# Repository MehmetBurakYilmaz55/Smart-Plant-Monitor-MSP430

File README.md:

# Akıllı Tarım Otomasyonu ve Gömülü Kontrol Sistemi (MSP430)

Bu proje, bir bitkinin çevresel ihtiyaçlarını (nem, sıcaklık, ışık) sürekli olarak analiz edip gerekli fiziksel müdahaleleri (sulama, yapay aydınlatma) otonom olarak gerçekleştiren donanım merkezli bir gömülü sistem projesidir. 

Projenin temel amacı, piyasadaki hazır sensör ve güç modülleri (breakout board) kullanım alışkanlıklarını bir kenara bırakarak; voltaj regülasyonundan güç anahtarlamaya kadar tüm elektriksel altyapının özel tasarlanmış **çift taraflı bir PCB** üzerinde komponent seviyesinde (component-level) birleştirilmesidir. Yazılım mimarisinde ise hiçbir soyutlama kütüphanesi (HAL veya standart kütüphane) kullanılmamış, doğrudan mikrodenetleyici register'larına müdahale edilmiştir.

---

## 🛠️ Donanım Mimarisi ve Çift Taraflı PCB Tasarımı

Sistemin en güçlü yönü, elektriksel bütünlüğü ve kararlılığı maksimize etmek amacıyla baştan sona özel olarak tasarlanan donanım altyapısıdır. Piyasada sıkça tercih edilen hazır modüllerden (Bluetooth ve OLED ekran hariç) tamamen kaçınılmış, sistem donanım seviyesinde sıfırdan kurgulanmıştır.

* **Çift Taraflı (Double-Sided) Özelleştirilmiş PCB:** Sinyal yolları ve yüksek akım çeken güç hatları, elektromanyetik girişimi (EMI) minimize edecek şekilde iki katmanlı olarak yönlendirilmiştir.
* **Tümleşik Voltaj Regülasyonu:** Harici bir güç modülü kullanılmaksızın, giriş gerilimini mikrodenetleyicinin ve sensörlerin ihtiyaç duyduğu kararlı 3.3V seviyesine düşüren lineer regülatör devresi doğrudan PCB üzerine gömülmüştür.
* **Komponent Seviyesinde Tasarım:** Hazır röle veya sensör kartları kullanılmamıştır. Su pompasını süren rölenin transistör tabanlı sürücü devresi (demeraj ve ters EMK korumaları dahil) ile sensör okuma hatlarının sinyal koşullandırma devreleri PCB üzerinde bağımsız komponentlerle dizayn edilmiştir.
* **Fiziksel Dayanım:** Ortam şartlarına ve elektromekanik titreşimlere karşı dirençli bir endüstriyel prototip elde edilmiştir.

---

## 💻 Yazılım Mimarisi (Bare-Metal)

Sistemin yazılımı, MSP430G2553 mikrodenetleyicisinin tüm kaynaklarını %100 kontrol edebilmek amacıyla tamamen **"Bare-Metal"** (kütüphanesiz) olarak C dilinde geliştirilmiştir.

* **Register-Level Programlama:** I2C, UART, ADC ve Timer donanımları hazır kütüphanelerle değil, doğrudan işlemci kaydedicileri (register) üzerinden bayt bayt yapılandırılmıştır.
* **Özel I2C ve OLED Sürücüsü:** SSD1306 OLED ekranı kontrol etmek için donanımsal I2C protokolü ve 5x8 ASCII font matrisi sıfırdan yazılarak sisteme entegre edilmiştir.
* **Donanımsal PWM Üretimi:** İşlemciyi döngüsel gecikmelerle (delay) yormamak adına, Timer_A modülü "Reset/Set" modunda (OUTMOD_7) çalıştırılarak pürüzsüz ve işlemciden bağımsız bir PWM sinyali elde edilmiştir.
* **Dinamik Sağlık Algoritması:** Sensörlerden alınan ham ADC verileri, lineer azalan ölçeklendirme matematiksel modeli ile işlenerek bitkinin anlık durumunu gösteren dinamik bir "Büyüme Kalitesi Puanına" dönüştürülür.
* **Histerezis Kontrolü:** Röle tetiklemelerinde sistemin kararsızlığa düşmesini (chatter effect) engellemek için yazılımsal ölü bölgeler (dead-zones) oluşturulmuştur.

---

## ⚙️ Temel Özellikler ve Otonom Fonksiyonlar

* **Akıllı Sulama:** Toprak nemi belirlenen kritik eşiğin altına düştüğünde su pompası devreye girer, ideal neme ulaşıldığında histerezis bandı sayesinde güvenli bir şekilde kapanır.
* **Ters Orantılı Aydınlatma:** Ortamdaki ışık (LDR) seviyesi düştükçe, PWM kontrollü yapay aydınlatma modülü otomatik olarak parlaklığını artırır.
* **Gerçek Zamanlı Telemetri:** Tüm sensör verileri, hesaplanan kalite puanı ve röle durumları Bluetooth (UART) üzerinden kablosuz olarak aktarılır.
* **Lokal Arayüz:** İşlenen veriler ve puan durumu, cihaz üzerindeki OLED ekranda anlık olarak görüntülenir.

---

## 🚀 Kullanılan Teknolojiler ve Bileşenler

* **Mikrodenetleyici:** Texas Instruments MSP430G2553
* **Sensör Ağı:** NTC (Sıcaklık), Analog Toprak Nemi Sensörü, LDR (Ortam Işığı)
* **Aktüatörler:** 5V Su Pompası (Transistör sürücülü röle ile kontrol edilir), LED Aydınlatma (Timer_A PWM destekli)
* **Haberleşme:** HC-05 / UART Bluetooth Modülü (Sadece modül olarak kullanılmıştır)
* **Görüntüleme:** 0.96" SSD1306 OLED (I2C) (Sadece modül olarak kullanılmıştır)
* **Geliştirme Ortamı:** Code Composer Studio (CCS)
* **PCB Tasarım:** KiCad

---

## 📂 Dosya ve Klasör Yapısı

Projenin donanım tasarımı, üretim çıktıları ve yazılım kaynak kodları modüler bir yapıda organize edilmiştir:

* **`C/`**: Sistemin beyni olan yazılımın bulunduğu dizindir. Herhangi bir hazır kütüphane kullanılmadan doğrudan register seviyesinde yazılmış Bare-Metal C kaynak kodlarını içerir.
* **`Docs/`**: Donanım tasarımının mutfağıdır. Devrenin **KiCad** üzerinde sıfırdan çizilmiş elektronik şematiklerini, çift taraflı PCB yerleşim (layout) planlarını ve lazer kazıma yöntemiyle üretime hazır hale getirilmiş ön/arka bakır (Cu) yüzey PDF çıktılarını barındırır.
* **`Images/`**: Teorik tasarımın fiziksel bir ürüne dönüşme serüvenini belgeler. Lazer kazıma makinesindeki üretim aşamalarından, montajı ve lehimlemesi bitmiş çift taraflı kartın detaylı fotoğraflarına kadar projenin donanımsal kalitesini gösteren görsel dökümanları içerir.

---

## 👨‍💻 Geliştirici

**Mehmet Burak Yılmaz** 
Kocaeli Üniversitesi - Elektronik ve Haberleşme Mühendisliği

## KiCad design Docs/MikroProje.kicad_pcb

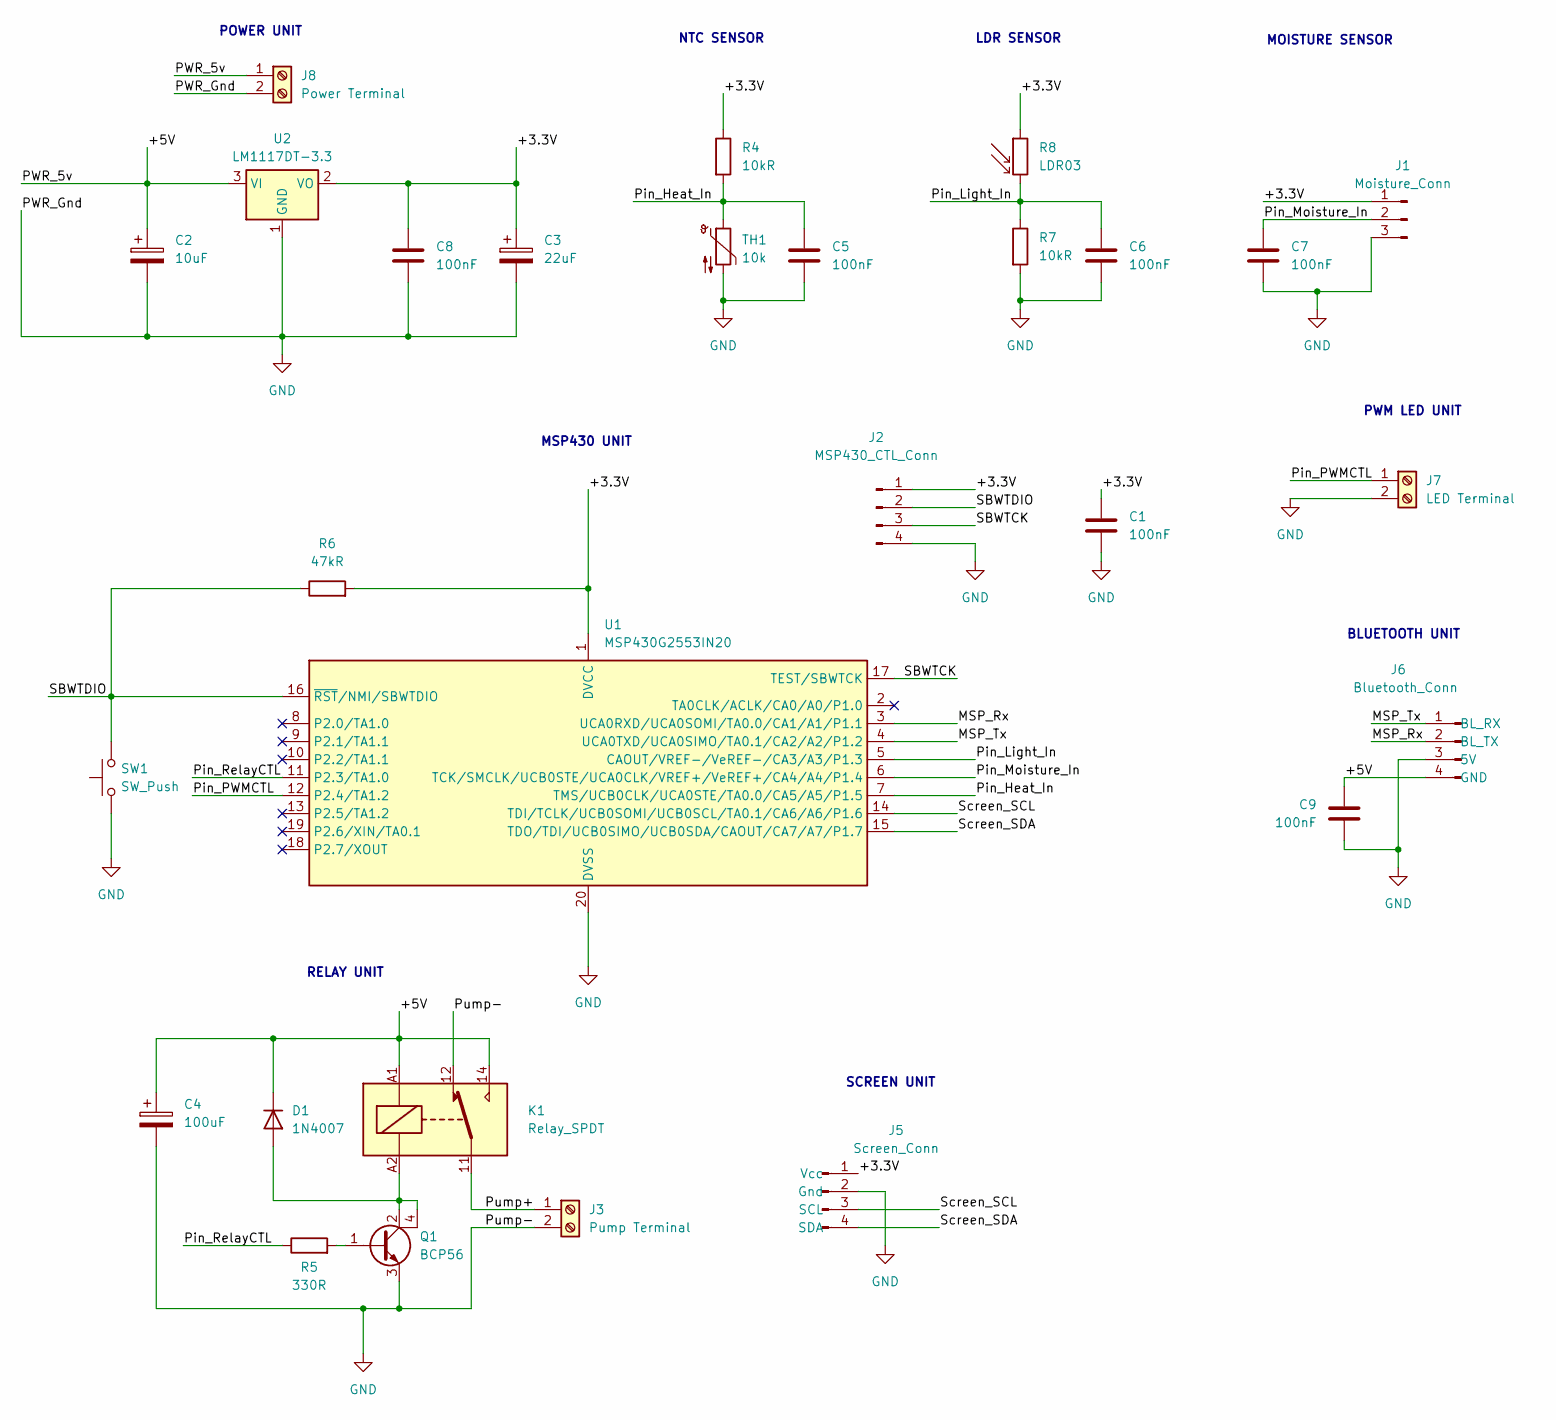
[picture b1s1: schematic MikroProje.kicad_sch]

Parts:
C1, C5, C6, C7, C8, C9: 100nF; C_1206_3216Metric_Pad1.33x1.80mm_HandSolder
C2: 10uF; CP_EIA-3528-21_Kemet-B_HandSolder
C3: 22uF; CP_EIA-3528-21_Kemet-B_HandSolder
C4: 100uF; CP_Radial_D5.0mm_P2.00mm
D1: 1N4007; D_SMA_Handsoldering
J1: Moisture_Conn; PinSocket_1x03_P2.54mm_Vertical
J2: MSP430_CTL_Conn; PinHeader_1x04_P2.54mm_Vertical
J3: Pump Terminal; TerminalBlock_Phoenix_MKDS-1,5-2-5.08_1x02_P5.08mm_Horizont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
J5: Screen_Conn; PinSocket_1x04_P2.54mm_Vertical
J6: Bluetooth_Conn; PinSocket_1x04_P2.54mm_Vertical
J7: LED Terminal; TerminalBlock_Phoenix_MKDS-1,5-2-5.08_1x02_P5.08mm_Horizont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
J8: Power Terminal; TerminalBlock_Phoenix_MKDS-1,5-2-5.08_1x02_P5.08mm_Horizont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
K1: Relay_SPDT; Relay_SPDT_Finder_32.21-x000
Q1: BCP56; SOT-223
R4, R7: 10kR; R_1206_3216Metric_Pad1.30x1.75mm_HandSolder
R5: 330R; R_1206_3216Metric_Pad1.30x1.75mm_HandSolder
R6: 47kR; R_1206_3216Metric_Pad1.30x1.75mm_HandSolder
R8: LDR03; R_LDR_5.0x4.1mm_P3mm_Vertical
SW1: SW_Push; SW_SPST_B3S-1000
TH1: 10k; R_1206_3216Metric_Pad1.30x1.75mm_HandSolder
U1: MSP430G2553IN20; DIP-20_W7.62mm
U2: LM1117DT-3.3; SOT-223-3_TabPin2

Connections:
/+3.3V: C1.1, C3.1, C8.1, J1.1, J2.1, J5.1 (Vcc), R4.1, R6.2, R8.1, U1.1 (DVCC), U2.2 (VO)
/+5V: C2.1, C4.1, C9.1, D1.1 (K), J6.4 (GND), J8.1, K1.14, K1.A1, U2.3 (VI)
/MSP_Rx: J6.2 (BL_TX), U1.3 (UCA0RXD/UCA0SOMI/TA0.0/CA1/A1/P1.1)
/MSP_Tx: J6.1 (BL_RX), U1.4 (UCA0TXD/UCA0SIMO/TA0.1/CA2/A2/P1.2)
/Pin_Heat_In: C5.1, R4.2, TH1.1, U1.7 (TMS/UCB0CLK/UCA0STE/TA0.0/CA5/A5/P1.5)
/Pin_Light_In: C6.1, R7.1, R8.2, U1.5 (CAOUT/VREF-/VeREF-/CA3/A3/P1.3)
/Pin_Moisture_In: C7.1, J1.2, U1.6 (TCK/SMCLK/UCB0STE/UCA0CLK/VREF+/VeREF+/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)
/Pin_PWMCTL: J7.1, U1.12 (P2.4/TA1.2)
/Pin_RelayCTL: R5.1, U1.11 (P2.3/TA1.0)
/Pump+: J3.1, K1.11
/SBWTCK: J2.3, U1.17 (TEST/SBWTCK)
/SBWTDIO: J2.2, R6.1, SW1.2, U1.16 (~RST/NMI/SBWTDIO)
/Screen_SCL: J5.3 (SCL), U1.14 (TDI/TCLK/UCB0SOMI/UCB0SCL/TA0.1/CA6/A6/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)
/Screen_SDA: J5.4 (SDA), U1.15 (TDO/TDI/UCB0SIMO/UCB0SDA/CAOUT/CA7/A7/P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)
GND: C1.2, C2.2, C3.2, C4.2, C5.2, C6.2, C7.2, C8.2, C9.2, J1.3, J2.4, J3.2, J5.2 (Gnd), J6.3 (5V), J7.2, J8.2, K1.12, Q1.3 (E), R7.2, SW1.1, TH1.2, U1.20 (DVSS), U2.1 (GND)
unnamed: D1.2 (A), K1.A2, Q1.2 (C), Q1.4 (C)
unnamed: Q1.1 (B), R5.2

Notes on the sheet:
BLUETOOTH UNIT
MOISTURE SENSOR
NTC SENSOR
MSP430 UNIT
LDR SENSOR
SCREEN UNIT
POWER UNIT
RELAY UNIT
PWM LED UNIT

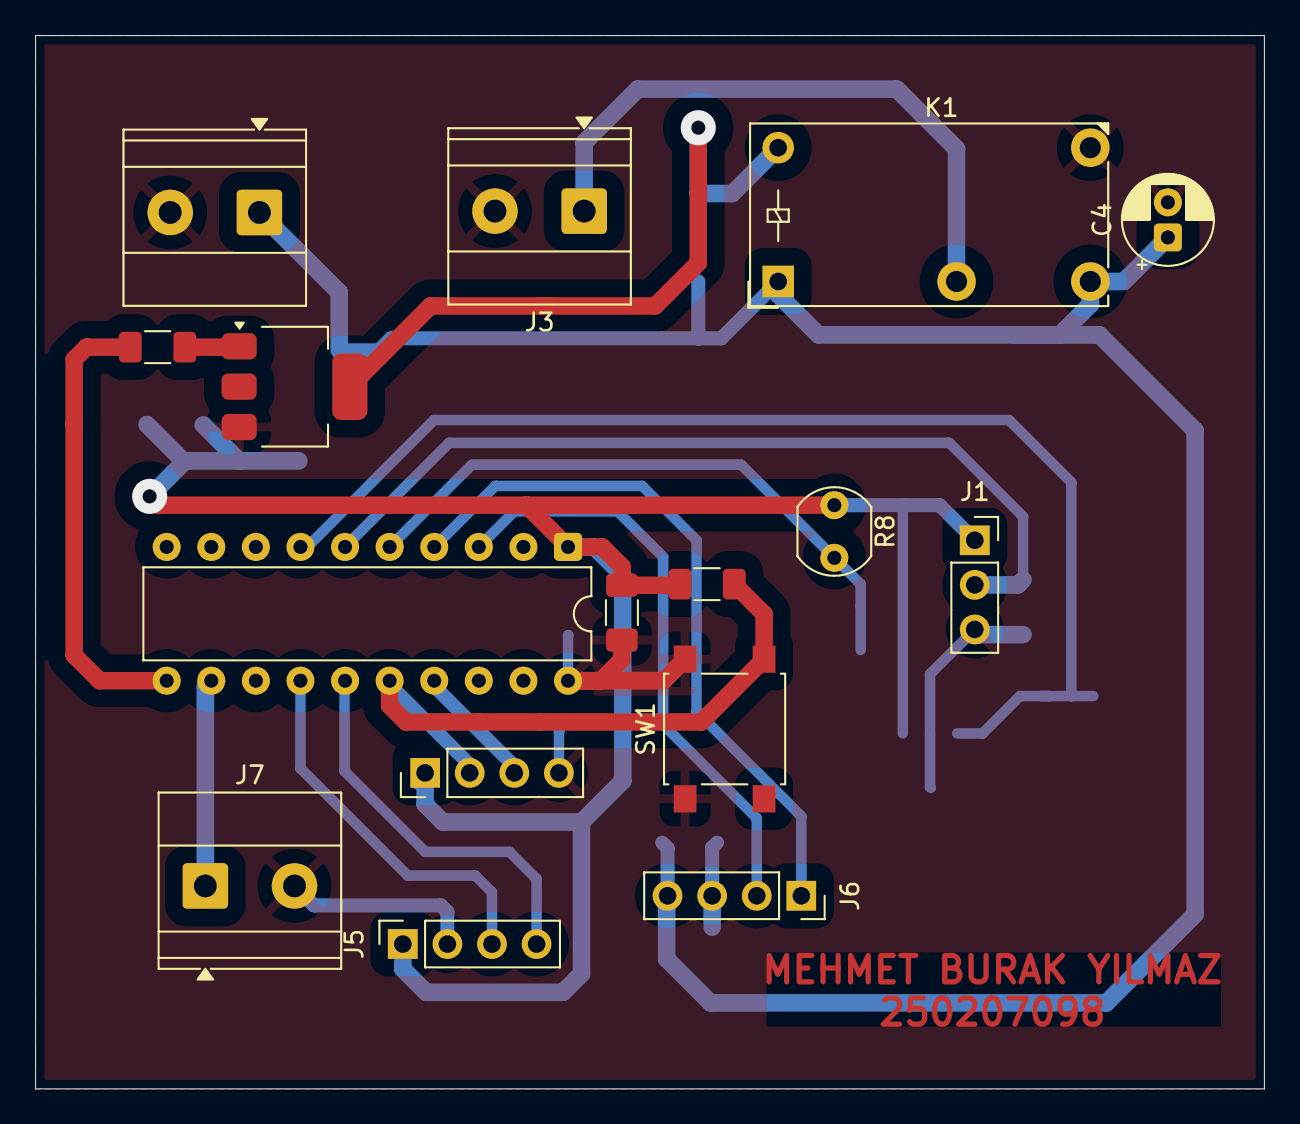
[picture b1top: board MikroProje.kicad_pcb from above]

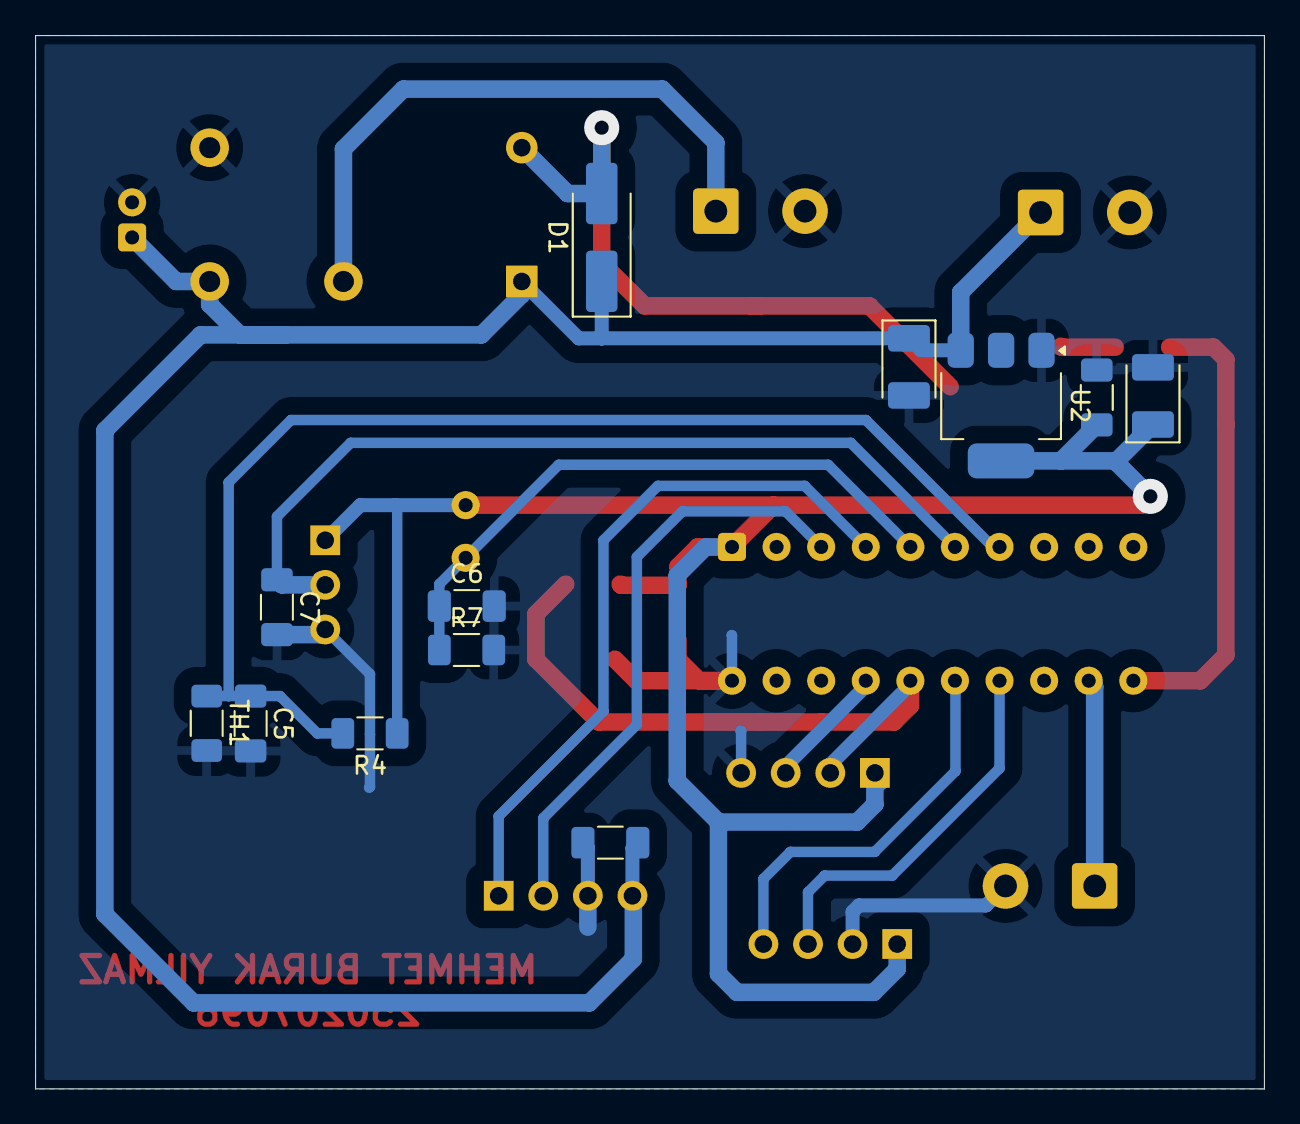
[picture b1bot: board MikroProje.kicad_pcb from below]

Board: 2 copper layers, 70.0 x 60.0 mm, 28 parts (12 on the bottom side), 17 nets.
